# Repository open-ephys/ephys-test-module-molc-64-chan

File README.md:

# Test Module for FOLC-based Headstages and Adapters

This test module works with the Open Ephys
[automated ephys tester](https://github.com/open-ephys/ephys-test-board). 
It can be used to verify the functionality of headstage-adapters and headstages that use the nanoZ/FOLC-110-01-S-Q_1 pinout.

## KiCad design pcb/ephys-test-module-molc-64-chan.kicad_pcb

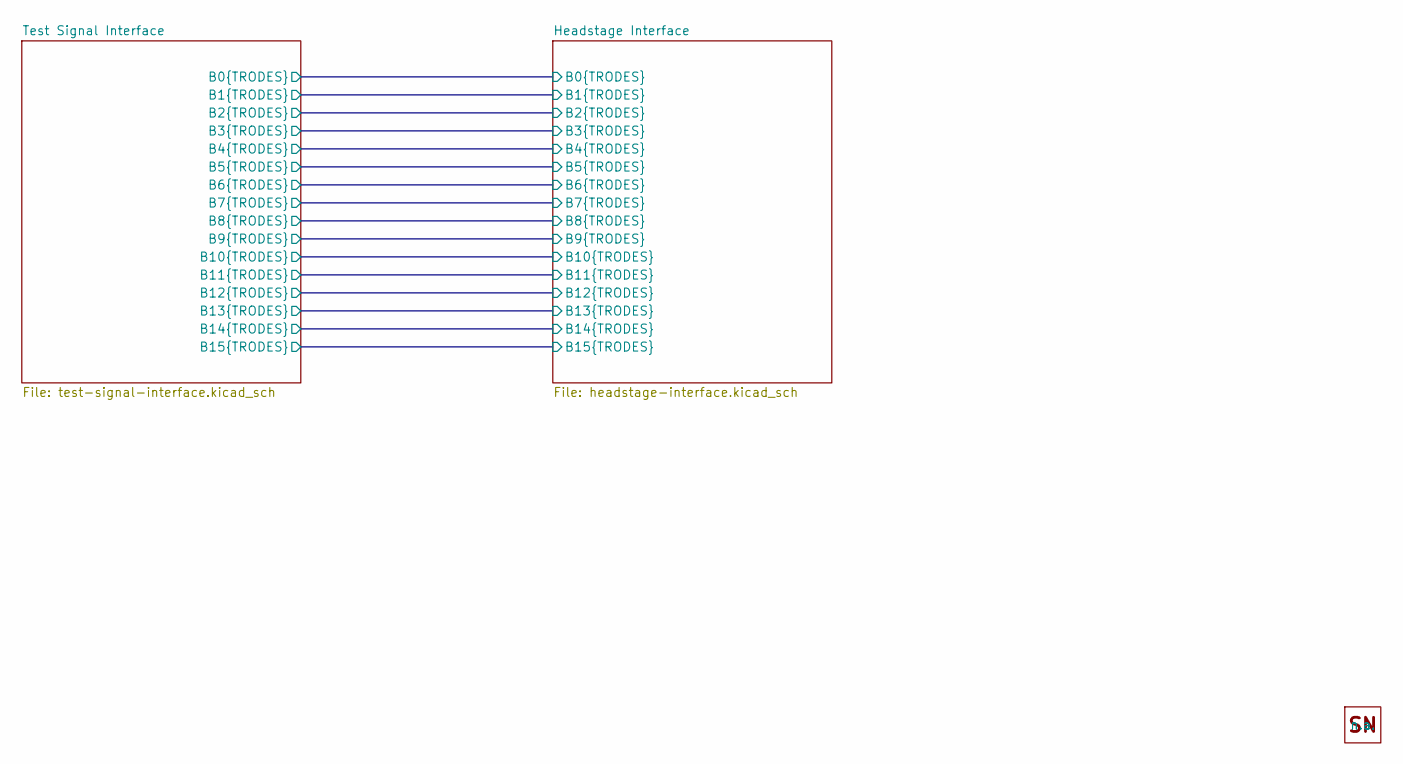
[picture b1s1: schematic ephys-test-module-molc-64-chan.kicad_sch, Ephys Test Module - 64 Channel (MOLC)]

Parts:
H1: OEPS_SN-STICKER-8x20mm; MPN n.a.

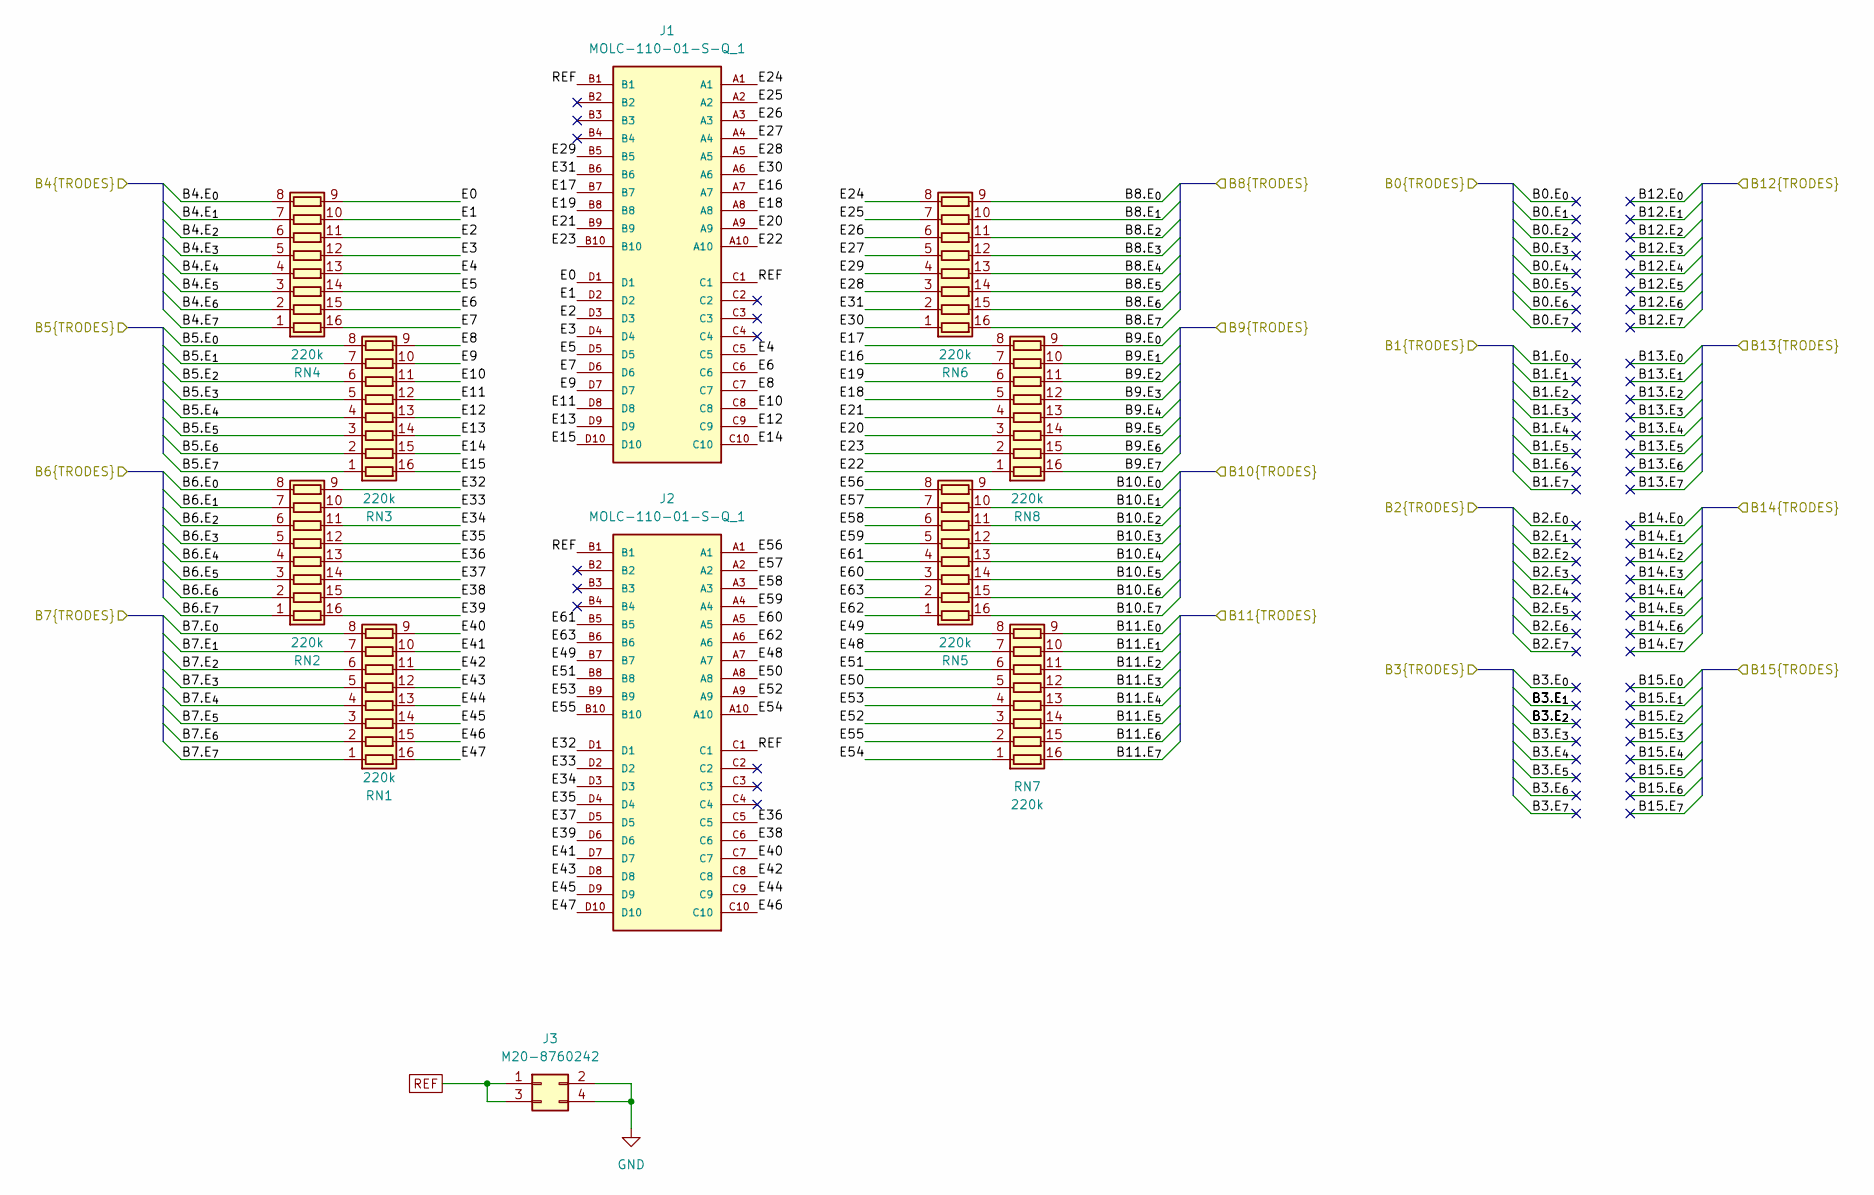
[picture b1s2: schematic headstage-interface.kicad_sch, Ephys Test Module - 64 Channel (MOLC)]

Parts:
J1, J2: MOLC-110-01-S-Q_1; SAMTEC_MOLC-110-01-S-Q; MPN MOLC-110-01-S-Q_1
J3: M20-8760242; PinHeader_2x02_P2.54mm_Vertical_SMD; MPN M20-8760242
RN1, RN2, RN3, RN4, RN5, RN6, RN7, RN8: 220k; R_Array_Convex_8x0602; Tolerance 5%; MPN YC248-JR-07220KL

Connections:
/Headstage Interface/B4.E_{0}: RN4.8 (R8.1); also elsewhere on the board
/Headstage Interface/B4.E_{1}: RN4.7 (R7.1); also elsewhere on the board
/Headstage Interface/B4.E_{2}: RN4.6 (R6.1); also elsewhere on the board
/Headstage Interface/B4.E_{3}: RN4.5 (R5.1); also elsewhere on the board
/Headstage Interface/B4.E_{4}: RN4.4 (R4.1); also elsewhere on the board
/Headstage Interface/B4.E_{5}: RN4.3 (R3.1); also elsewhere on the board
/Headstage Interface/B4.E_{6}: RN4.2 (R2.1); also elsewhere on the board
/Headstage Interface/B4.E_{7}: RN4.1 (R1.1); also elsewhere on the board
/Headstage Interface/B5.E_{0}: RN3.8 (R8.1); also elsewhere on the board
/Headstage Interface/B5.E_{1}: RN3.7 (R7.1); also elsewhere on the board
/Headstage Interface/B5.E_{2}: RN3.6 (R6.1); also elsewhere on the board
/Headstage Interface/B5.E_{3}: RN3.5 (R5.1); also elsewhere on the board
/Headstage Interface/B5.E_{4}: RN3.4 (R4.1); also elsewhere on the board
/Headstage Interface/B5.E_{5}: RN3.3 (R3.1); also elsewhere on the board
/Headstage Interface/B5.E_{6}: RN3.2 (R2.1); also elsewhere on the board
/Headstage Interface/B5.E_{7}: RN3.1 (R1.1); also elsewhere on the board
/Headstage Interface/B6.E_{0}: RN2.8 (R8.1); also elsewhere on the board
/Headstage Interface/B6.E_{1}: RN2.7 (R7.1); also elsewhere on the board
/Headstage Interface/B6.E_{2}: RN2.6 (R6.1); also elsewhere on the board
/Headstage Interface/B6.E_{3}: RN2.5 (R5.1); also elsewhere on the board
/Headstage Interface/B6.E_{4}: RN2.4 (R4.1); also elsewhere on the board
/Headstage Interface/B6.E_{5}: RN2.3 (R3.1); also elsewhere on the board
/Headstage Interface/B6.E_{6}: RN2.2 (R2.1); also elsewhere on the board
/Headstage Interface/B6.E_{7}: RN2.1 (R1.1); also elsewhere on the board
/Headstage Interface/B7.E_{0}: RN1.8 (R8.1); also elsewhere on the board
/Headstage Interface/B7.E_{1}: RN1.7 (R7.1); also elsewhere on the board
/Headstage Interface/B7.E_{2}: RN1.6 (R6.1); also elsewhere on the board
/Headstage Interface/B7.E_{3}: RN1.5 (R5.1); also elsewhere on the board
/Headstage Interface/B7.E_{4}: RN1.4 (R4.1); also elsewhere on the board
/Headstage Interface/B7.E_{5}: RN1.3 (R3.1); also elsewhere on the board
/Headstage Interface/B7.E_{6}: RN1.2 (R2.1); also elsewhere on the board
/Headstage Interface/B7.E_{7}: RN1.1 (R1.1); also elsewhere on the board
/Headstage Interface/B8.E_{0}: RN6.9 (R8.2); also elsewhere on the board
/Headstage Interface/B8.E_{1}: RN6.10 (R7.2); also elsewhere on the board
/Headstage Interface/B8.E_{2}: RN6.11 (R6.2); also elsewhere on the board
/Headstage Interface/B8.E_{3}: RN6.12 (R5.2); also elsewhere on the board
/Headstage Interface/B8.E_{4}: RN6.13 (R4.2); also elsewhere on the board
/Headstage Interface/B8.E_{5}: RN6.14 (R3.2); also elsewhere on the board
/Headstage Interface/B8.E_{6}: RN6.15 (R2.2); also elsewhere on the board
/Headstage Interface/B8.E_{7}: RN6.16 (R1.2); also elsewhere on the board
/Headstage Interface/B9.E_{0}: RN8.9 (R8.2); also elsewhere on the board
/Headstage Interface/B9.E_{1}: RN8.10 (R7.2); also elsewhere on the board
/Headstage Interface/B9.E_{2}: RN8.11 (R6.2); also elsewhere on the board
/Headstage Interface/B9.E_{3}: RN8.12 (R5.2); also elsewhere on the board
/Headstage Interface/B9.E_{4}: RN8.13 (R4.2); also elsewhere on the board
/Headstage Interface/B9.E_{5}: RN8.14 (R3.2); also elsewhere on the board
/Headstage Interface/B9.E_{6}: RN8.15 (R2.2); also elsewhere on the board
/Headstage Interface/B9.E_{7}: RN8.16 (R1.2); also elsewhere on the board
/Headstage Interface/B10.E_{0}: RN5.9 (R8.2); also elsewhere on the board
/Headstage Interface/B10.E_{1}: RN5.10 (R7.2); also elsewhere on the board
/Headstage Interface/B10.E_{2}: RN5.11 (R6.2); also elsewhere on the board
/Headstage Interface/B10.E_{3}: RN5.12 (R5.2); also elsewhere on the board
/Headstage Interface/B10.E_{4}: RN5.13 (R4.2); also elsewhere on the board
/Headstage Interface/B10.E_{5}: RN5.14 (R3.2); also elsewhere on the board
/Headstage Interface/B10.E_{6}: RN5.15 (R2.2); also elsewhere on the board
/Headstage Interface/B10.E_{7}: RN5.16 (R1.2); also elsewhere on the board
/Headstage Interface/B11.E_{0}: RN7.9 (R8.2); also elsewhere on the board
/Headstage Interface/B11.E_{1}: RN7.10 (R7.2); also elsewhere on the board
/Headstage Interface/B11.E_{2}: RN7.11 (R6.2); also elsewhere on the board
/Headstage Interface/B11.E_{3}: RN7.12 (R5.2); also elsewhere on the board
/Headstage Interface/B11.E_{4}: RN7.13 (R4.2); also elsewhere on the board
/Headstage Interface/B11.E_{5}: RN7.14 (R3.2); also elsewhere on the board
/Headstage Interface/B11.E_{6}: RN7.15 (R2.2); also elsewhere on the board
/Headstage Interface/B11.E_{7}: RN7.16 (R1.2); also elsewhere on the board
/Headstage Interface/E0: J1.D1, RN4.9 (R8.2)
/Headstage Interface/E1: J1.D2, RN4.10 (R7.2)
/Headstage Interface/E2: J1.D3, RN4.11 (R6.2)
/Headstage Interface/E3: J1.D4, RN4.12 (R5.2)
/Headstage Interface/E4: J1.C5, RN4.13 (R4.2)
/Headstage Interface/E5: J1.D5, RN4.14 (R3.2)
/Headstage Interface/E6: J1.C6, RN4.15 (R2.2)
/Headstage Interface/E7: J1.D6, RN4.16 (R1.2)
/Headstage Interface/E8: J1.C7, RN3.9 (R8.2)
/Headstage Interface/E9: J1.D7, RN3.10 (R7.2)
/Headstage Interface/E10: J1.C8, RN3.11 (R6.2)
/Headstage Interface/E11: J1.D8, RN3.12 (R5.2)
/Headstage Interface/E12: J1.C9, RN3.13 (R4.2)
/Headstage Interface/E13: J1.D9, RN3.14 (R3.2)
/Headstage Interface/E14: J1.C10, RN3.15 (R2.2)
/Headstage Interface/E15: J1.D10, RN3.16 (R1.2)
/Headstage Interface/E16: J1.A7, RN8.7 (R7.1)
/Headstage Interface/E17: J1.B7, RN8.8 (R8.1)
/Headstage Interface/E18: J1.A8, RN8.5 (R5.1)
/Headstage Interface/E19: J1.B8, RN8.6 (R6.1)
/Headstage Interface/E20: J1.A9, RN8.3 (R3.1)
/Headstage Interface/E21: J1.B9, RN8.4 (R4.1)
/Headstage Interface/E22: J1.A10, RN8.1 (R1.1)
/Headstage Interface/E23: J1.B10, RN8.2 (R2.1)
/Headstage Interface/E24: J1.A1, RN6.8 (R8.1)
/Headstage Interface/E25: J1.A2, RN6.7 (R7.1)
/Headstage Interface/E26: J1.A3, RN6.6 (R6.1)
/Headstage Interface/E27: J1.A4, RN6.5 (R5.1)
/Headstage Interface/E28: J1.A5, RN6.3 (R3.1)
/Headstage Interface/E29: J1.B5, RN6.4 (R4.1)
/Headstage Interface/E30: J1.A6, RN6.1 (R1.1)
/Headstage Interface/E31: J1.B6, RN6.2 (R2.1)
/Headstage Interface/E32: J2.D1, RN2.9 (R8.2)
/Headstage Interface/E33: J2.D2, RN2.10 (R7.2)
/Headstage Interface/E34: J2.D3, RN2.11 (R6.2)
/Headstage Interface/E35: J2.D4, RN2.12 (R5.2)
/Headstage Interface/E36: J2.C5, RN2.13 (R4.2)
/Headstage Interface/E37: J2.D5, RN2.14 (R3.2)
/Headstage Interface/E38: J2.C6, RN2.15 (R2.2)
/Headstage Interface/E39: J2.D6, RN2.16 (R1.2)
/Headstage Interface/E40: J2.C7, RN1.9 (R8.2)
/Headstage Interface/E41: J2.D7, RN1.10 (R7.2)
/Headstage Interface/E42: J2.C8, RN1.11 (R6.2)
/Headstage Interface/E43: J2.D8, RN1.12 (R5.2)
/Headstage Interface/E44: J2.C9, RN1.13 (R4.2)
/Headstage Interface/E45: J2.D9, RN1.14 (R3.2)
/Headstage Interface/E46: J2.C10, RN1.15 (R2.2)
/Headstage Interface/E47: J2.D10, RN1.16 (R1.2)
/Headstage Interface/E48: J2.A7, RN7.7 (R7.1)
/Headstage Interface/E49: J2.B7, RN7.8 (R8.1)
/Headstage Interface/E50: J2.A8, RN7.5 (R5.1)
/Headstage Interface/E51: J2.B8, RN7.6 (R6.1)
/Headstage Interface/E52: J2.A9, RN7.3 (R3.1)
/Headstage Interface/E53: J2.B9, RN7.4 (R4.1)
/Headstage Interface/E54: J2.A10, RN7.1 (R1.1)
/Headstage Interface/E55: J2.B10, RN7.2 (R2.1)
/Headstage Interface/E56: J2.A1, RN5.8 (R8.1)
/Headstage Interface/E57: J2.A2, RN5.7 (R7.1)
/Headstage Interface/E58: J2.A3, RN5.6 (R6.1)
/Headstage Interface/E59: J2.A4, RN5.5 (R5.1)
/Headstage Interface/E60: J2.A5, RN5.3 (R3.1)
/Headstage Interface/E61: J2.B5, RN5.4 (R4.1)
/Headstage Interface/E62: J2.A6, RN5.1 (R1.1)
/Headstage Interface/E63: J2.B6, RN5.2 (R2.1)
GND: J3.2, J3.4; also elsewhere on the board
REF: J1.B1, J1.C1, J2.B1, J2.C1, J3.1, J3.3; also elsewhere on the board

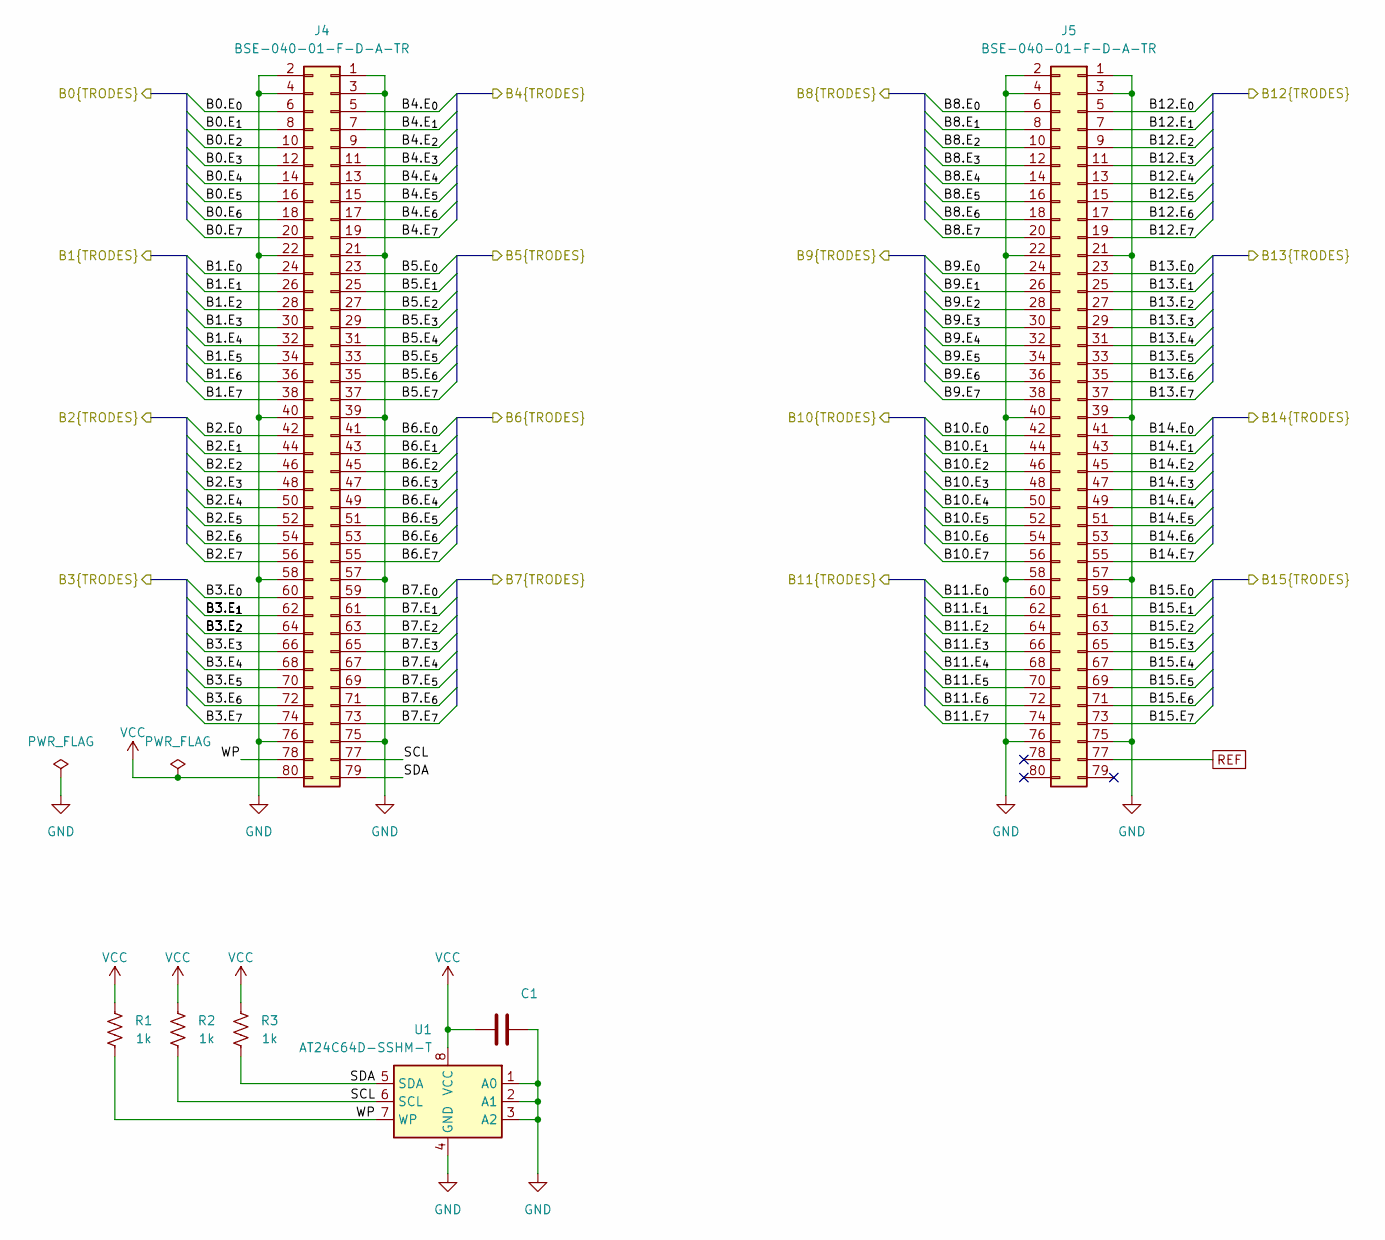
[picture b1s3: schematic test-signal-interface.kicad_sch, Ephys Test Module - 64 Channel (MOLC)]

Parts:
C1: 100nF; C_0402_1005Metric; Tolerance X5R; MPN C1005X5R1V104K050BB
J4, J5: BSE-040-01-F-D-A-TR; SAMTEC_BSE-040-01-X-D-A; MPN BSE-040-01-F-D-A-TR
R1, R2, R3: 1k; R_0402_1005Metric; Tolerance 1%; MPN CRCW04021K00FKED
U1: AT24C64D-SSHM-T; SOIC-8_3.9x4.9mm_P1.27mm; MPN AT24C64D-SSHM-T

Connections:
/Headstage Interface/B0.E_{0}: J4.6
/Headstage Interface/B0.E_{1}: J4.8
/Headstage Interface/B0.E_{2}: J4.10
/Headstage Interface/B0.E_{3}: J4.12
/Headstage Interface/B0.E_{4}: J4.14
/Headstage Interface/B0.E_{5}: J4.16
/Headstage Interface/B0.E_{6}: J4.18
/Headstage Interface/B0.E_{7}: J4.20
/Headstage Interface/B1.E_{0}: J4.24
/Headstage Interface/B1.E_{1}: J4.26
/Headstage Interface/B1.E_{2}: J4.28
/Headstage Interface/B1.E_{3}: J4.30
/Headstage Interface/B1.E_{4}: J4.32
/Headstage Interface/B1.E_{5}: J4.34
/Headstage Interface/B1.E_{6}: J4.36
/Headstage Interface/B1.E_{7}: J4.38
/Headstage Interface/B2.E_{0}: J4.42
/Headstage Interface/B2.E_{1}: J4.44
/Headstage Interface/B2.E_{2}: J4.46
/Headstage Interface/B2.E_{3}: J4.48
/Headstage Interface/B2.E_{4}: J4.50
/Headstage Interface/B2.E_{5}: J4.52
/Headstage Interface/B2.E_{6}: J4.54
/Headstage Interface/B2.E_{7}: J4.56
/Headstage Interface/B3.E_{0}: J4.60
/Headstage Interface/B3.E_{1}: J4.62
/Headstage Interface/B3.E_{2}: J4.64
/Headstage Interface/B3.E_{3}: J4.66
/Headstage Interface/B3.E_{4}: J4.68
/Headstage Interface/B3.E_{5}: J4.70
/Headstage Interface/B3.E_{6}: J4.72
/Headstage Interface/B3.E_{7}: J4.74
/Headstage Interface/B4.E_{0}: J4.5; also elsewhere on the board
/Headstage Interface/B4.E_{1}: J4.7; also elsewhere on the board
/Headstage Interface/B4.E_{2}: J4.9; also elsewhere on the board
/Headstage Interface/B4.E_{3}: J4.11; also elsewhere on the board
/Headstage Interface/B4.E_{4}: J4.13; also elsewhere on the board
/Headstage Interface/B4.E_{5}: J4.15; also elsewhere on the board
/Headstage Interface/B4.E_{6}: J4.17; also elsewhere on the board
/Headstage Interface/B4.E_{7}: J4.19; also elsewhere on the board
/Headstage Interface/B5.E_{0}: J4.23; also elsewhere on the board
/Headstage Interface/B5.E_{1}: J4.25; also elsewhere on the board
/Headstage Interface/B5.E_{2}: J4.27; also elsewhere on the board
/Headstage Interface/B5.E_{3}: J4.29; also elsewhere on the board
/Headstage Interface/B5.E_{4}: J4.31; also elsewhere on the board
/Headstage Interface/B5.E_{5}: J4.33; also elsewhere on the board
/Headstage Interface/B5.E_{6}: J4.35; also elsewhere on the board
/Headstage Interface/B5.E_{7}: J4.37; also elsewhere on the board
/Headstage Interface/B6.E_{0}: J4.41; also elsewhere on the board
/Headstage Interface/B6.E_{1}: J4.43; also elsewhere on the board
/Headstage Interface/B6.E_{2}: J4.45; also elsewhere on the board
/Headstage Interface/B6.E_{3}: J4.47; also elsewhere on the board
/Headstage Interface/B6.E_{4}: J4.49; also elsewhere on the board
/Headstage Interface/B6.E_{5}: J4.51; also elsewhere on the board
/Headstage Interface/B6.E_{6}: J4.53; also elsewhere on the board
/Headstage Interface/B6.E_{7}: J4.55; also elsewhere on the board
/Headstage Interface/B7.E_{0}: J4.59; also elsewhere on the board
/Headstage Interface/B7.E_{1}: J4.61; also elsewhere on the board
/Headstage Interface/B7.E_{2}: J4.63; also elsewhere on the board
/Headstage Interface/B7.E_{3}: J4.65; also elsewhere on the board
/Headstage Interface/B7.E_{4}: J4.67; also elsewhere on the board
/Headstage Interface/B7.E_{5}: J4.69; also elsewhere on the board
/Headstage Interface/B7.E_{6}: J4.71; also elsewhere on the board
/Headstage Interface/B7.E_{7}: J4.73; also elsewhere on the board
/Headstage Interface/B8.E_{0}: J5.6; also elsewhere on the board
/Headstage Interface/B8.E_{1}: J5.8; also elsewhere on the board
/Headstage Interface/B8.E_{2}: J5.10; also elsewhere on the board
/Headstage Interface/B8.E_{3}: J5.12; also elsewhere on the board
/Headstage Interface/B8.E_{4}: J5.14; also elsewhere on the board
/Headstage Interface/B8.E_{5}: J5.16; also elsewhere on the board
/Headstage Interface/B8.E_{6}: J5.18; also elsewhere on the board
/Headstage Interface/B8.E_{7}: J5.20; also elsewhere on the board
/Headstage Interface/B9.E_{0}: J5.24; also elsewhere on the board
/Headstage Interface/B9.E_{1}: J5.26; also elsewhere on the board
/Headstage Interface/B9.E_{2}: J5.28; also elsewhere on the board
/Headstage Interface/B9.E_{3}: J5.30; also elsewhere on the board
/Headstage Interface/B9.E_{4}: J5.32; also elsewhere on the board
/Headstage Interface/B9.E_{5}: J5.34; also elsewhere on the board
/Headstage Interface/B9.E_{6}: J5.36; also elsewhere on the board
/Headstage Interface/B9.E_{7}: J5.38; also elsewhere on the board
/Headstage Interface/B10.E_{0}: J5.42; also elsewhere on the board
/Headstage Interface/B10.E_{1}: J5.44; also elsewhere on the board
/Headstage Interface/B10.E_{2}: J5.46; also elsewhere on the board
/Headstage Interface/B10.E_{3}: J5.48; also elsewhere on the board
/Headstage Interface/B10.E_{4}: J5.50; also elsewhere on the board
/Headstage Interface/B10.E_{5}: J5.52; also elsewhere on the board
/Headstage Interface/B10.E_{6}: J5.54; also elsewhere on the board
/Headstage Interface/B10.E_{7}: J5.56; also elsewhere on the board
/Headstage Interface/B11.E_{0}: J5.60; also elsewhere on the board
/Headstage Interface/B11.E_{1}: J5.62; also elsewhere on the board
/Headstage Interface/B11.E_{2}: J5.64; also elsewhere on the board
/Headstage Interface/B11.E_{3}: J5.66; also elsewhere on the board
/Headstage Interface/B11.E_{4}: J5.68; also elsewhere on the board
/Headstage Interface/B11.E_{5}: J5.70; also elsewhere on the board
/Headstage Interface/B11.E_{6}: J5.72; also elsewhere on the board
/Headstage Interface/B11.E_{7}: J5.74; also elsewhere on the board
/Headstage Interface/B12.E_{0}: J5.5
/Headstage Interface/B12.E_{1}: J5.7
/Headstage Interface/B12.E_{2}: J5.9
/Headstage Interface/B12.E_{3}: J5.11
/Headstage Interface/B12.E_{4}: J5.13
/Headstage Interface/B12.E_{5}: J5.15
/Headstage Interface/B12.E_{6}: J5.17
/Headstage Interface/B12.E_{7}: J5.19
/Headstage Interface/B13.E_{0}: J5.23
/Headstage Interface/B13.E_{1}: J5.25
/Headstage Interface/B13.E_{2}: J5.27
/Headstage Interface/B13.E_{3}: J5.29
/Headstage Interface/B13.E_{4}: J5.31
/Headstage Interface/B13.E_{5}: J5.33
/Headstage Interface/B13.E_{6}: J5.35
/Headstage Interface/B13.E_{7}: J5.37
/Headstage Interface/B14.E_{0}: J5.41
/Headstage Interface/B14.E_{1}: J5.43
/Headstage Interface/B14.E_{2}: J5.45
/Headstage Interface/B14.E_{3}: J5.47
/Headstage Interface/B14.E_{4}: J5.49
/Headstage Interface/B14.E_{5}: J5.51
/Headstage Interface/B14.E_{6}: J5.53
/Headstage Interface/B14.E_{7}: J5.55
/Headstage Interface/B15.E_{0}: J5.59
/Headstage Interface/B15.E_{1}: J5.61
/Headstage Interface/B15.E_{2}: J5.63
/Headstage Interface/B15.E_{3}: J5.65
/Headstage Interface/B15.E_{4}: J5.67
/Headstage Interface/B15.E_{5}: J5.69
/Headstage Interface/B15.E_{6}: J5.71
/Headstage Interface/B15.E_{7}: J5.73
/Test Signal Interface/SCL: J4.77, R2.2, U1.6 (SCL)
/Test Signal Interface/SDA: J4.79, R3.2, U1.5 (SDA)
/Test Signal Interface/WP: J4.78, R1.2, U1.7 (WP)
GND: C1.2, J4.1, J4.2, J4.3, J4.4, J4.21, J4.22, J4.39, J4.40, J4.57, J4.58, J4.75, J4.76, J5.1, J5.2, J5.3, J5.4, J5.21, J5.22, J5.39, J5.40, J5.57, J5.58, J5.75, J5.76, U1.1 (A0), U1.2 (A1), U1.3 (A2), U1.4 (GND); also elsewhere on the board
REF: J5.77; also elsewhere on the board
VCC: C1.1, J4.80, R1.1, R2.1, R3.1, U1.8 (VCC)

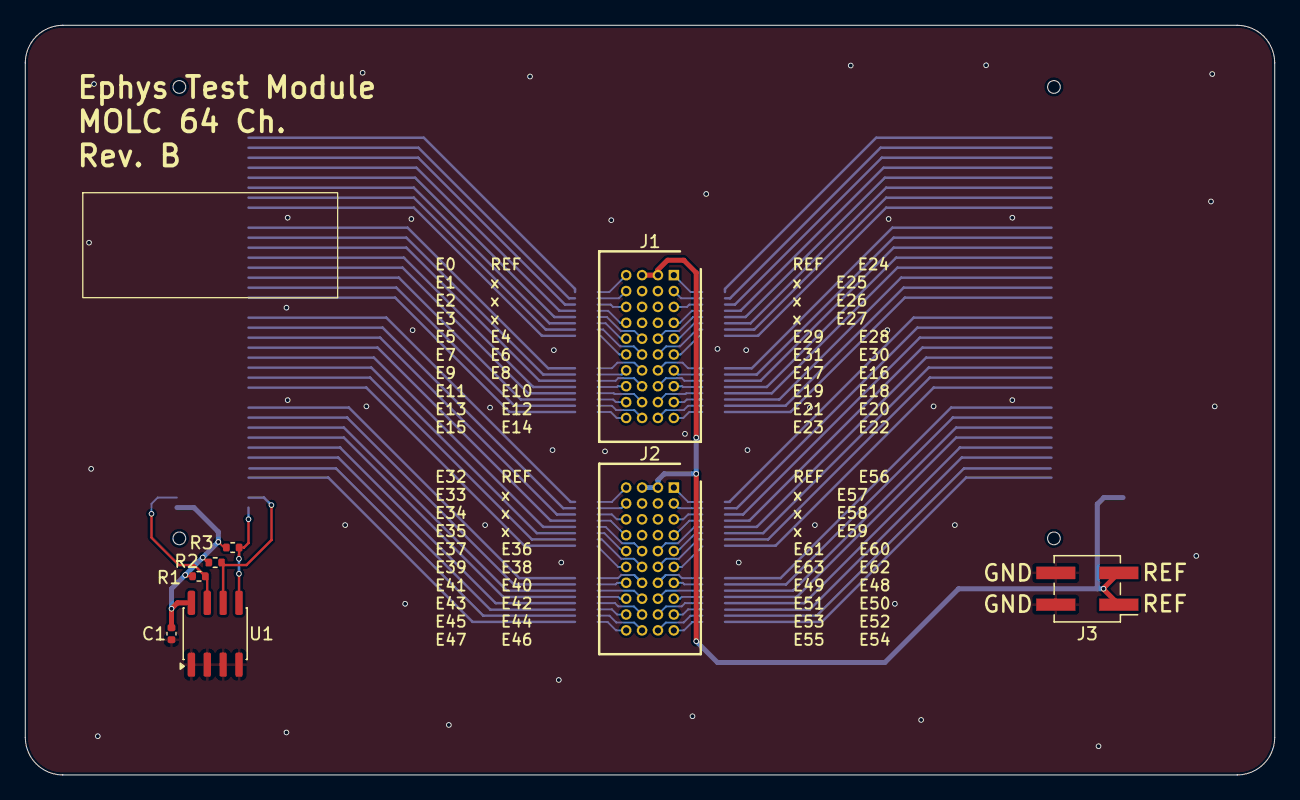
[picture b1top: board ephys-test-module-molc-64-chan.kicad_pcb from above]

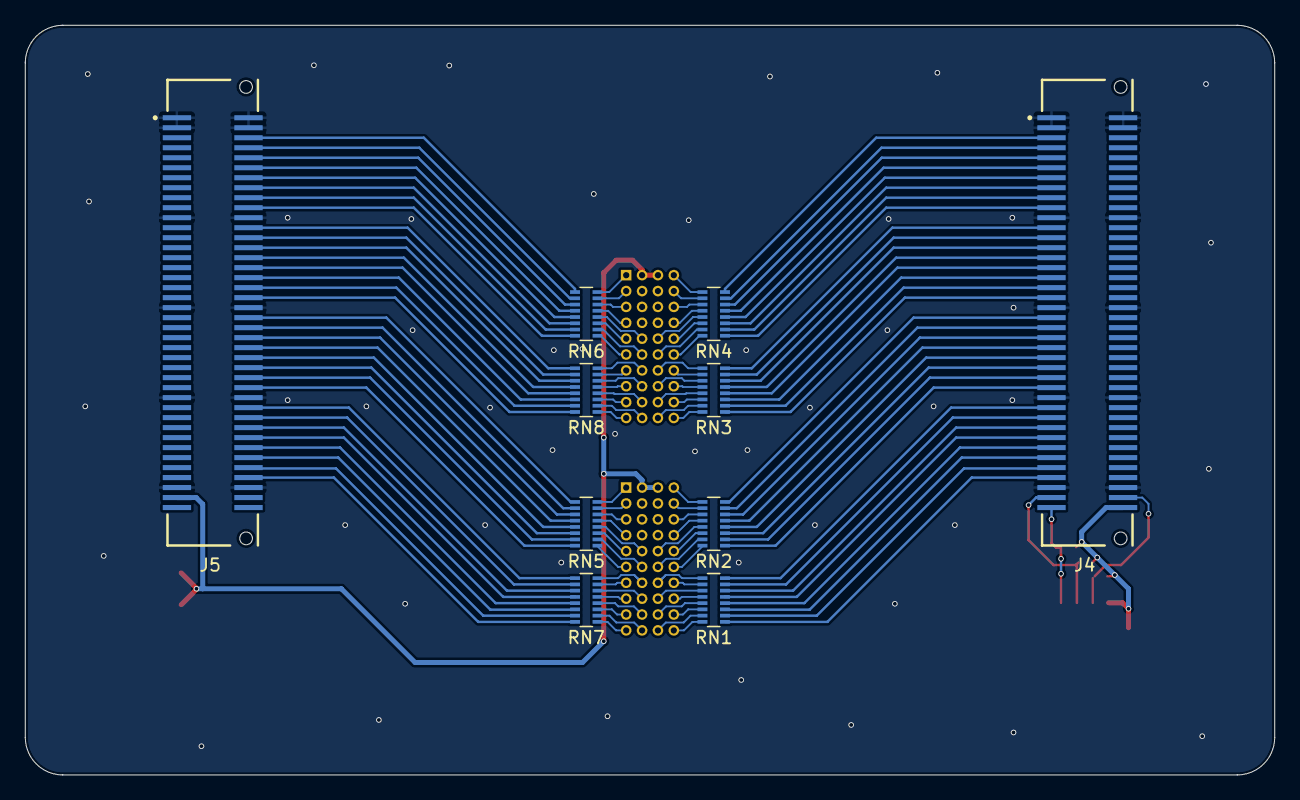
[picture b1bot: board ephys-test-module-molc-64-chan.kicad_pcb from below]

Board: 2 copper layers, 100.0 x 60.0 mm, 19 parts (10 on the bottom side), 134 nets.

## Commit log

2025-10-01 Revision A
2025-10-08 Add pdf of the schematic
2025-10-24 Revision B
    - Added 220k resistor arrays in series with amplifier connections to
    simulate electrodes
2025-10-24 Add EEPROM programmer
    - This includes two channel maps. The first is the standard nano-z
    channel map. The second maps to the low-profile heastage (DF40) map
    through MOLC adapter board.
2025-11-03 Revision B
    - Widened traces to 0.2 mm
